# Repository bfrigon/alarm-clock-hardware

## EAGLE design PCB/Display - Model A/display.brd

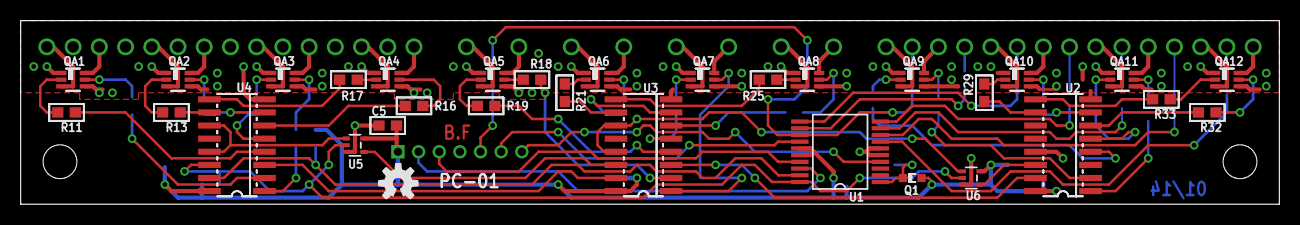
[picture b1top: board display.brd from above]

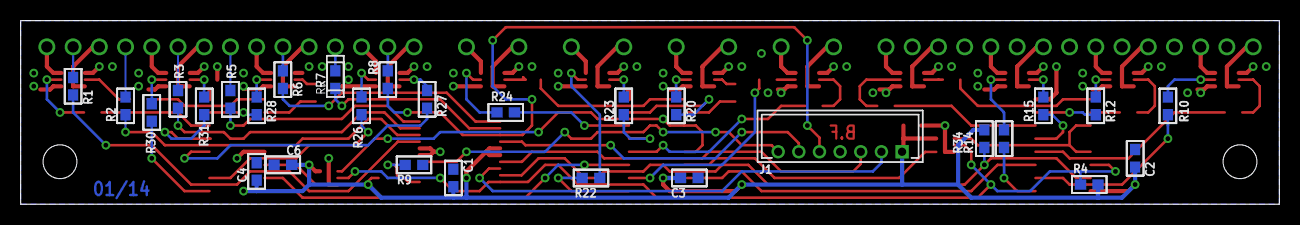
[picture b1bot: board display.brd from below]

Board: 2 copper layers, 121.9 x 17.8 mm, 64 parts (30 on the bottom side), 101 nets.

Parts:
C1, C2, C3, C4, C5, C6: 100nF; SMD_0603
J1: SNG-2MM-HEADER-07-V; DF3X-7P-2DSA
Q1: ALS-PT19
QA1, QA2, QA3, QA4, QA5, QA6, QA7, QA8, QA9, QA10, QA11, QA12: MMDT3904; SOT363
R1, R2, R3, R5, R6, R7, R8: 47; SMD_0603
R4, R10, R11, R12, R13, R14, R15, R16, R17, R18, R19, R20, R21, R22, R23, R24, R25, R26, R27, R28, R29, R30, R31, R32, R33, R34: 1k; SMD_0603
R9: 10k; SMD_0603
U1: PIC16F1826-I/SS; SSOP20
U2, U3, U4: 74HC4017D; SOIC16N
U5, U6: 74LVC1G08DCKR; SC70-5
U$1: LED_MATRIX_V_24X7
U$3: OPENHW_LOGO_150
U$6: INFO_DATE
U$7: INFO_AUTHOR

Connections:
3.3V: C1.1, C2.2, C3.2, C4.2, C5.1, C6.1, J1.1, Q1.C, R4.2, R34.2, U1.15, U1.16, U2.16, U3.16, U4.16, U5.5, U6.5
COL_CLK: R4.1, U1.20, U4.14, U5.2, U6.2
COL_MR: R34.1, U1.19, U4.15
GND: C1.2, C2.1, C3.1, C4.1, C5.2, C6.2, J1.4, QA1.1, QA1.4, QA2.1, QA2.4, QA3.1, QA3.4, QA4.1, QA4.4, QA5.1, QA5.4, QA6.1, QA6.4, QA7.1, QA7.4, QA8.1, QA8.4, QA9.1, QA9.4, QA10.1, QA10.4, QA11.1, QA11.4, QA12.1, QA12.4, R9.1, U1.5, U1.6, U2.8, U2.13, U3.8, U4.8, U5.3, U6.3
unnamed: R8.2, U$1.A7@2
unnamed: R7.2, U$1.A6@2
unnamed: R6.2, U$1.A5@2
unnamed: R5.2, U$1.A4@2
unnamed: R3.2, U$1.A3@2
unnamed: R2.2, U$1.A2@2
unnamed: R1.2, U$1.A1@2
unnamed: Q1.E, R9.2, U1.1
unnamed: QA12.6, U$1.C24
unnamed: QA12.3, U$1.C23
unnamed: QA11.6, U$1.C22
unnamed: QA11.3, U$1.C21
unnamed: QA10.6, U$1.C20
unnamed: QA10.3, U$1.C19
unnamed: QA9.6, U$1.C18
unnamed: QA9.3, U$1.C17
unnamed: QA8.6, U$1.C16
unnamed: QA8.3, U$1.C15
unnamed: QA7.6, U$1.C14
unnamed: QA7.3, U$1.C13
unnamed: QA6.6, U$1.C12
unnamed: QA6.3, U$1.C11
unnamed: QA5.6, U$1.C10
unnamed: QA5.3, U$1.C9
unnamed: QA4.6, U$1.C8
unnamed: QA4.3, U$1.C7
unnamed: QA3.6, U$1.C6
unnamed: QA3.3, U$1.C5
unnamed: QA2.6, U$1.C4
unnamed: QA2.3, U$1.C3
unnamed: QA1.6, U$1.C2
unnamed: QA1.3, U$1.C1
unnamed: QA9.5, R26.2
unnamed: QA9.2, R27.2
unnamed: QA10.5, R28.2
unnamed: QA10.2, R29.2
unnamed: QA11.5, R30.2
unnamed: QA11.2, R31.2
unnamed: QA12.5, R32.2
unnamed: QA12.2, R33.2
unnamed: QA8.2, R25.2
unnamed: QA8.5, R24.2
unnamed: QA7.2, R23.2
unnamed: QA7.5, R22.2
unnamed: QA6.2, R21.2
unnamed: QA6.5, R20.2
unnamed: R10.1, U4.2
unnamed: QA5.2, R19.2
unnamed: QA5.5, R18.2
unnamed: QA4.2, R17.2
unnamed: QA4.5, R16.2
unnamed: QA3.2, R15.2
unnamed: QA3.5, R14.2
unnamed: QA2.2, R13.2
unnamed: QA2.5, R12.2
unnamed: QA1.2, R11.2
unnamed: QA1.5, R10.2
unnamed: U4.11, U4.13, U5.1
unnamed: U3.14, U5.4
unnamed: U3.15, U4.3
unnamed: U2.15, U3.3
unnamed: U3.11, U3.13, U6.1
unnamed: U2.14, U6.4
unnamed: R11.1, U4.4
unnamed: R12.1, U4.7
unnamed: R13.1, U4.10
unnamed: R14.1, U4.1
unnamed: R15.1, U4.5
unnamed: R16.1, U4.6
unnamed: R17.1, U4.9
unnamed: R18.1, U3.2
unnamed: R19.1, U3.4
unnamed: R21.1, U3.10
unnamed: R20.1, U3.7
unnamed: R22.1, U3.1
unnamed: R23.1, U3.5
unnamed: R24.1, U3.6
unnamed: R25.1, U3.9
unnamed: R26.1, U2.2
unnamed: R27.1, U2.4
unnamed: R28.1, U2.7
unnamed: R29.1, U2.10
unnamed: R30.1, U2.1
unnamed: R31.1, U2.5
unnamed: R32.1, U2.6
unnamed: R33.1, U2.9
PGD: J1.6, U1.14
ROW1: R1.1, U1.7
ROW2: R2.1, U1.8
ROW3: R3.1, U1.9
ROW4: R5.1, U1.10
ROW5: R6.1, U1.11
ROW6: R7.1, U1.12
ROW7/PGC: J1.5, R8.1, U1.13
SCL: J1.3, U1.17
SDA: J1.2, U1.18
VPP/!MCLR: J1.7, U1.4

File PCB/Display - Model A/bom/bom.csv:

'Qty.';'Part ID';'Description';'Mfg. SKU';'Manufacturer';'Package';'Value';
'1';'Q1';'Ambiant light sensor';'ALS-PT19-315C/L177/TR8';'Everlight';'ALS-PT19';'-';
'1';'J1';'2mm Single Row Header - 7 pos - SMT Vertical';'DF3X-7P-2DSA';'Hirose Electronic';'DF3X-7P-2DSA';'-';
'2';'U5, U6';'2-input AND gate';'SN74LVC1G08DCKR';'Texas Instruments';'SC70-5';'-';
'3';'U2, U3, U4';'Johnson decade counter';'74HC4017D';'NXP Semiconductors';'SOIC16N';'-';
'12';'QA2, QA1, QA3, QA4, QA5, QA6, QA7, QA8, QA9, QA10, QA11, QA12';'NPN transistor - dual';'MMDT3904-7-F';'Diodes Inc.';'SOT363';'-';
'1';'U1';'20 Pin Flash Microcontroller';'PIC16F1826-I/SS';'Microchip';'SSOP20';'-';
'26';'R4, R10, R11, R12, R13, R14, R15, R16, R17, R18, R19, R20, R21, R22, R23, R24, R25, R26, R27, R28, R29, R30, R31, R32, R33, R34';'Resistor - SMT 0603 - 1k';'-';'-';'SMT 0603';'1k';
'1';'R9';'Resistor - SMT 0603 - 10k';'-';'-';'SMT 0603';'10k';
'7';'R1, R2, R3, R5, R6, R7, R8';'Resistor - SMT 0603 - 47';'-';'-';'SMT 0603';'47';
'6';'C1, C2, C3, C4, C5, C6';'Capacitor - SMT 0603 - 100nF';'-';'-';'SMT 0603';'100nF';

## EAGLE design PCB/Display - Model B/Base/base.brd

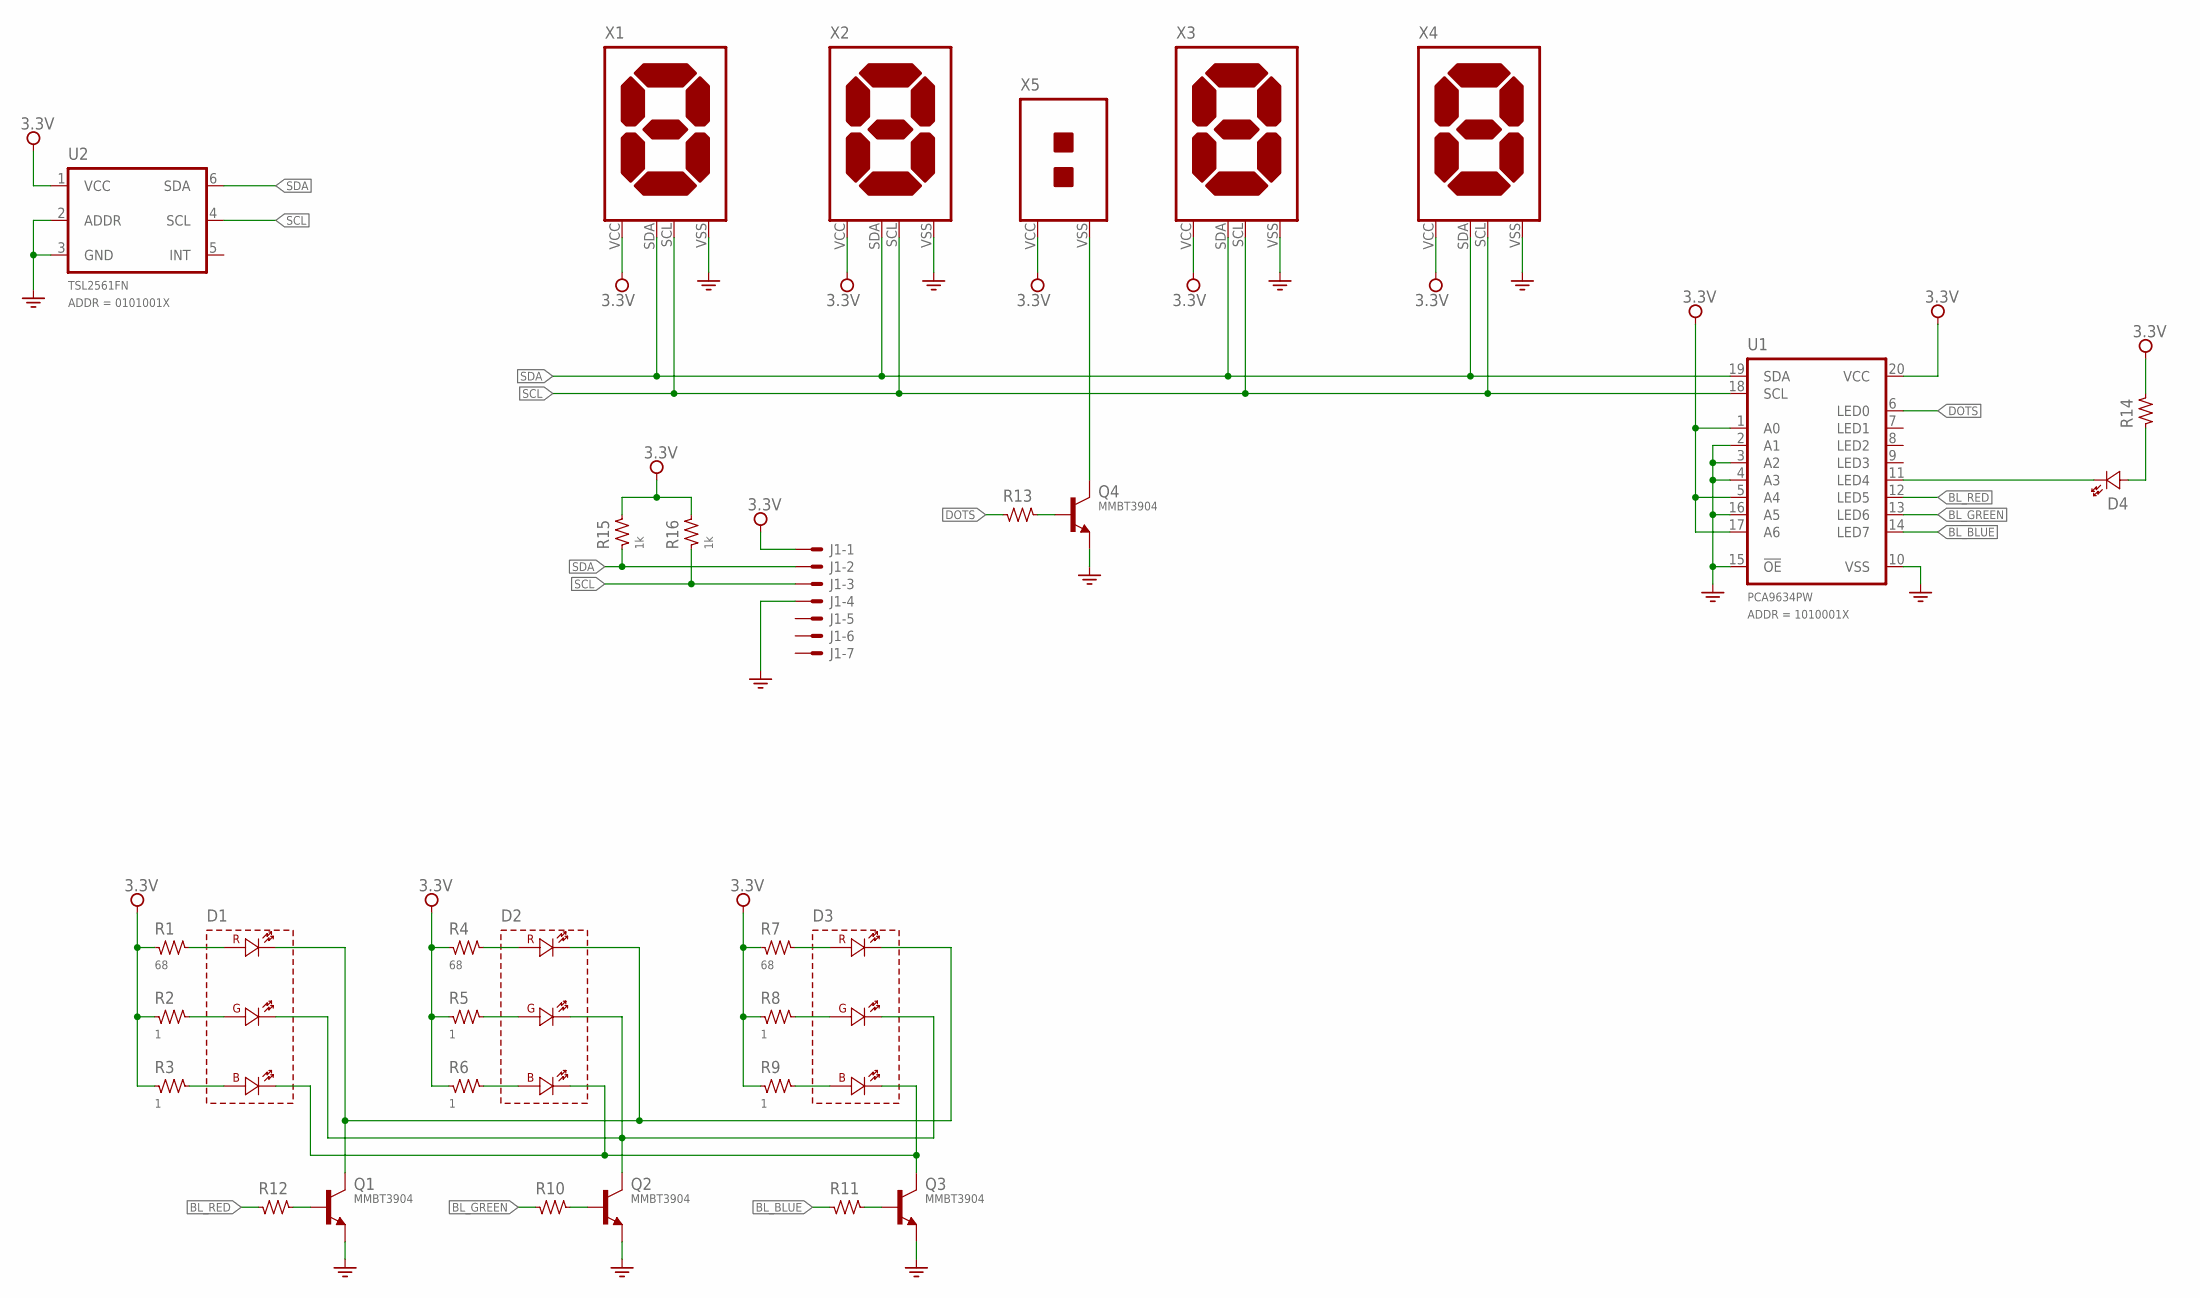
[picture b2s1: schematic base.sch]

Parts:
D1, D2, D3: SMP6-RGB; LED_RGB_PLCC6
D4: {ATTR:COLOR}; LED_3MM
J1: SNG-2MM-HEADER-07-V; DF3X-7P-2DSA; PART_NO DF3A-7P-2DSA
Q1, Q2, Q3, Q4: MMBT3904; SOT23
R1, R4, R7: 68; SMD_0603
R2, R3, R5, R6, R8, R9: 1; SMD_0603
R10, R11, R12, R13, R14: RES-0603; SMD_0603
R15, R16: 1k; SMD_0603
U1: PCA9634PW; TSSOP20
U2: TSL2561FN; DFN-6
X1, X2, X3, X4: CLOCK_LED_SEGMENT
X5: CLOCK_LED_DOTS

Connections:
3.3V: J1.1, R1.1, R2.1, R3.1, R4.1, R5.1, R6.1, R7.1, R8.1, R9.1, R14.2, R15.2, R16.2, U1.1 (A0), U1.5 (A4), U1.17 (A6), U1.20 (VCC), U2.1 (VCC), X1.VCC, X2.VCC, X3.VCC, X4.VCC, X5.VCC
BL_BLUE: R11.1, U1.14 (LED7)
BL_GREEN: R10.1, U1.13 (LED6)
BL_RED: R12.1, U1.12 (LED5)
DOTS: R13.1, U1.6 (LED0)
GND: J1.4, Q1.2 (E), Q2.2 (E), Q3.2 (E), Q4.2 (E), U1.2 (A1), U1.3 (A2), U1.4 (A3), U1.10 (VSS), U1.15 (!OE), U1.16 (A5), U2.2 (ADDR), U2.3 (GND), X1.VSS, X2.VSS, X3.VSS, X4.VSS
unnamed: D1.2 (GA), R2.2
unnamed: D1.4 (RA), R1.2
unnamed: D1.6 (BA), R3.2
unnamed: D2.4 (RA), R4.2
unnamed: D1.1 (GK), D2.1 (GK), D3.1 (GK), Q2.3 (C)
unnamed: D1.5 (BK), D2.5 (BK), D3.5 (BK), Q3.3 (C)
unnamed: D2.2 (GA), R5.2
unnamed: D2.6 (BA), R6.2
unnamed: D3.6 (BA), R9.2
unnamed: D3.2 (GA), R8.2
unnamed: D3.4 (RA), R7.2
unnamed: D1.3 (RK), D2.3 (RK), D3.3 (RK), Q1.3 (C)
unnamed: Q2.1 (B), R10.2
unnamed: Q3.1 (B), R11.2
unnamed: Q4.3 (C), X5.VSS
unnamed: Q4.1 (B), R13.2
unnamed: Q1.1 (B), R12.2
unnamed: D4.K, U1.11 (LED4)
unnamed: D4.A, R14.1
SCL: J1.3, R16.1, U1.18 (SCL), U2.4 (SCL), X1.SCL, X2.SCL, X3.SCL, X4.SCL
SDA: J1.2, R15.1, U1.19 (SDA), U2.6 (SDA), X1.SDA, X2.SDA, X3.SDA, X4.SDA

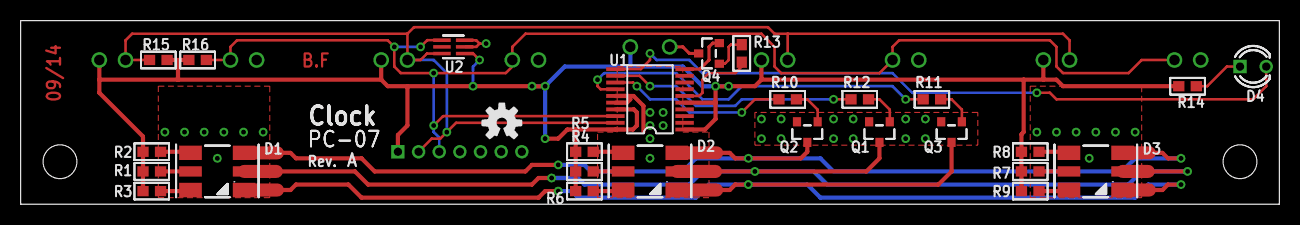
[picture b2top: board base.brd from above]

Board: 2 copper layers, 121.9 x 17.8 mm, 36 parts (1 on the bottom side), 27 nets.

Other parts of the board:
U$1: INFO_DATE
U$3: OPENHW_LOGO_150
U$4: INFO_COMPACT
U$5: INFO_AUTHOR

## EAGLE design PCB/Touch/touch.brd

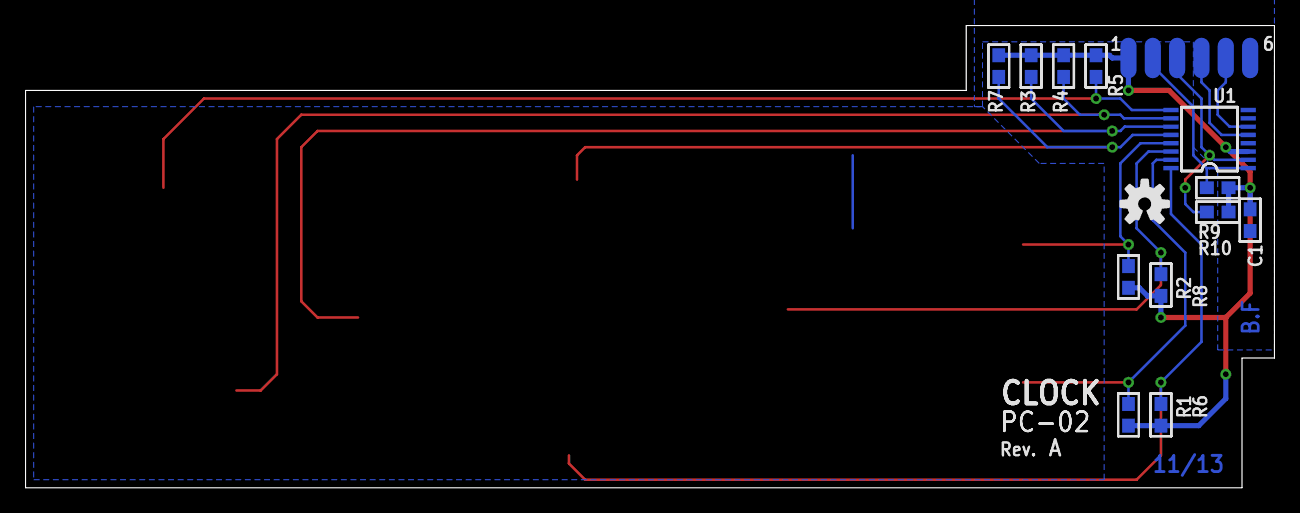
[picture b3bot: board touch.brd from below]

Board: 2 copper layers, 97.8 x 36.2 mm, 22 parts (22 on the bottom side), 14 nets.

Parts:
3.3V: 1; WIRE_SMT
!ATTN: 2; WIRE_SMT
!IRQ: 3; WIRE_SMT
C1: 1uF; SMD_0603
R1, R2, R3, R4, R5, R6, R7, R8: 780k; SMD_0603
R9, R10: 4.7k; SMD_0603
SCL: 4; WIRE_SMT
SDA: 5; WIRE_SMT
U1: MPR084EJ; TSSOP16
U$1: INFO_AUTHOR
U$2: INFO_DATE
U$3: INFO_COMPACT
U$5: OPENHW_LOGO_150
W6: 6; WIRE_SMT

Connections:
3.3V: 3.3V.1, C1.2, R1.2, R2.2, R3.2, R4.2, R5.2, R6.2, R7.2, R8.2, R9.2, R10.2, U1.3
!ATTN: !ATTN.1, R9.1, U1.1
!IRQ: !IRQ.1, R10.1, U1.2
E_ALARM: R4.1, U1.10
E_DOWN: R6.1, U1.16
E_HOUR: R2.1, U1.13
E_LEFT: R8.1, U1.14
E_MIN: R1.1, U1.15
E_RIGHT: R3.1, U1.11
E_TIME: R5.1, U1.9
E_UP: R7.1, U1.12
GND: C1.1, U1.4, U1.7, W6.1
SCL: SCL.1, U1.5
SDA: SDA.1, U1.6

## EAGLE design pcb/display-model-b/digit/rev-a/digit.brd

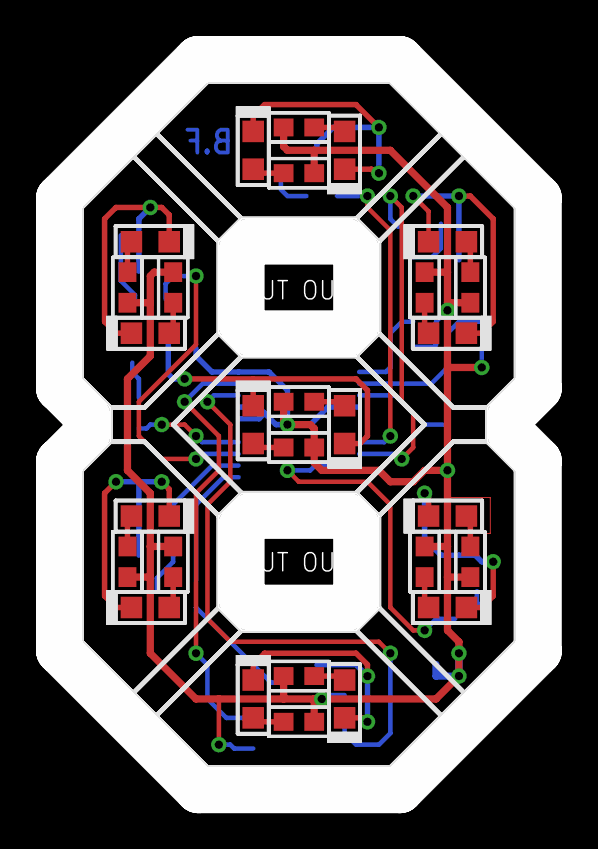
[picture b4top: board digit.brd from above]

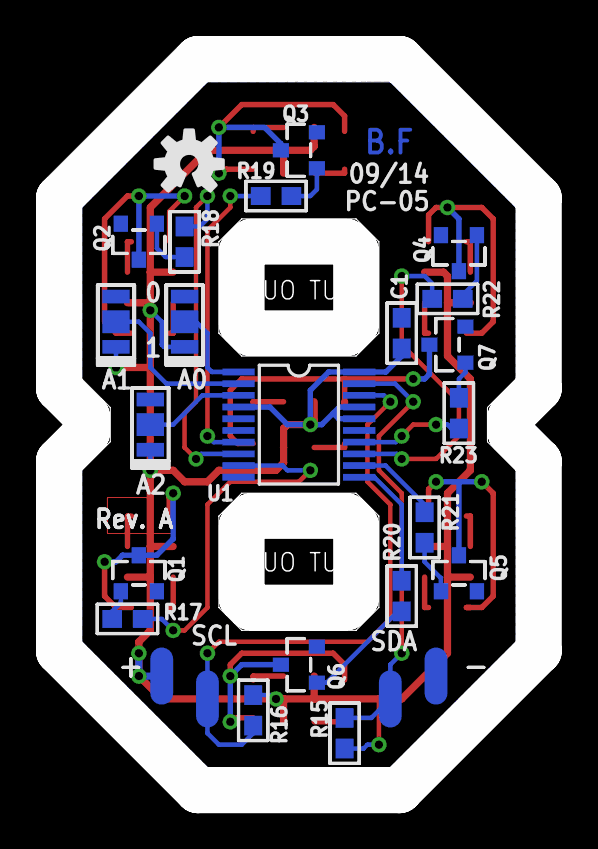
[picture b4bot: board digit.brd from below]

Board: 2 copper layers, 26.7 x 40.6 mm, 55 parts (27 on the bottom side), 42 nets.

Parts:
C1: 100nF; SMD_0603
D1, D2, D3, D4, D5, D6, D7, D8, D9, D10, D11, D12, D13, D14: Red; CHIPLED_0805
J1, J2, J3: SOLDER_JUMPER_3
Q1, Q2, Q3, Q4, Q5, Q6, Q7: MMBT3904; SOT23
R1, R2, R3, R4, R5, R6, R7, R8, R9, R10, R11, R12, R13, R14: 56; SMD_0603
R15, R16: N/A; SMD_0603
R17, R18, R19, R20, R21, R22, R23: 3k; SMD_0603
U1: PCA9634PW; TSSOP20
U$1: OPENHW_LOGO_150
U$2: INFO_AUTHOR
W1, W2, W3, W4: WIRE_SMT

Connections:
3.3V: C1.1, J1.1, J2.1, J3.1, R1.1, R2.1, R3.1, R4.1, R5.1, R6.1, R7.1, R8.1, R9.1, R10.1, R11.1, R12.1, R13.1, R14.1, R15.2, R16.2, U1.4, U1.16, U1.17, U1.20, W1.1
A0: J2.2, U1.1
A1: J1.2, U1.2
A2: J3.2, U1.3
GND: C1.2, J1.3, J2.3, J3.3, Q1.2, Q2.2, Q3.2, Q4.2, Q5.2, Q6.2, Q7.2, U1.5, U1.10, U1.15, W4.1
unnamed: Q1.1, R17.2
unnamed: D7.K, D8.K, Q4.3
unnamed: D13.K, D14.K, Q7.3
unnamed: D1.K, D2.K, Q1.3
unnamed: D3.K, D4.K, Q2.3
unnamed: D5.K, D6.K, Q3.3
unnamed: D3.A, R3.2
unnamed: D4.A, R4.2
unnamed: D14.A, R14.2
unnamed: D13.A, R13.2
unnamed: D2.A, R2.2
unnamed: D1.A, R1.2
unnamed: D5.A, R5.2
unnamed: D6.A, R6.2
unnamed: D11.A, R11.2
unnamed: D9.K, D10.K, Q5.3
unnamed: D11.K, D12.K, Q6.3
unnamed: D12.A, R12.2
unnamed: D10.A, R10.2
unnamed: D9.A, R9.2
unnamed: D7.A, R7.2
unnamed: D8.A, R8.2
unnamed: Q2.1, R18.2
unnamed: Q3.1, R19.2
unnamed: Q6.1, R20.2
unnamed: Q5.1, R21.2
unnamed: Q4.1, R22.2
unnamed: Q7.1, R23.2
SCL: R16.1, U1.18, W3.1
SDA: R15.1, U1.19, W2.1
SEG_A: R19.1, U1.7
SEG_B: R18.1, U1.8
SEG_C: R17.1, U1.9
SEG_D: R20.1, U1.11
SEG_E: R21.1, U1.12
SEG_F: R22.1, U1.13
SEG_G: R23.1, U1.14

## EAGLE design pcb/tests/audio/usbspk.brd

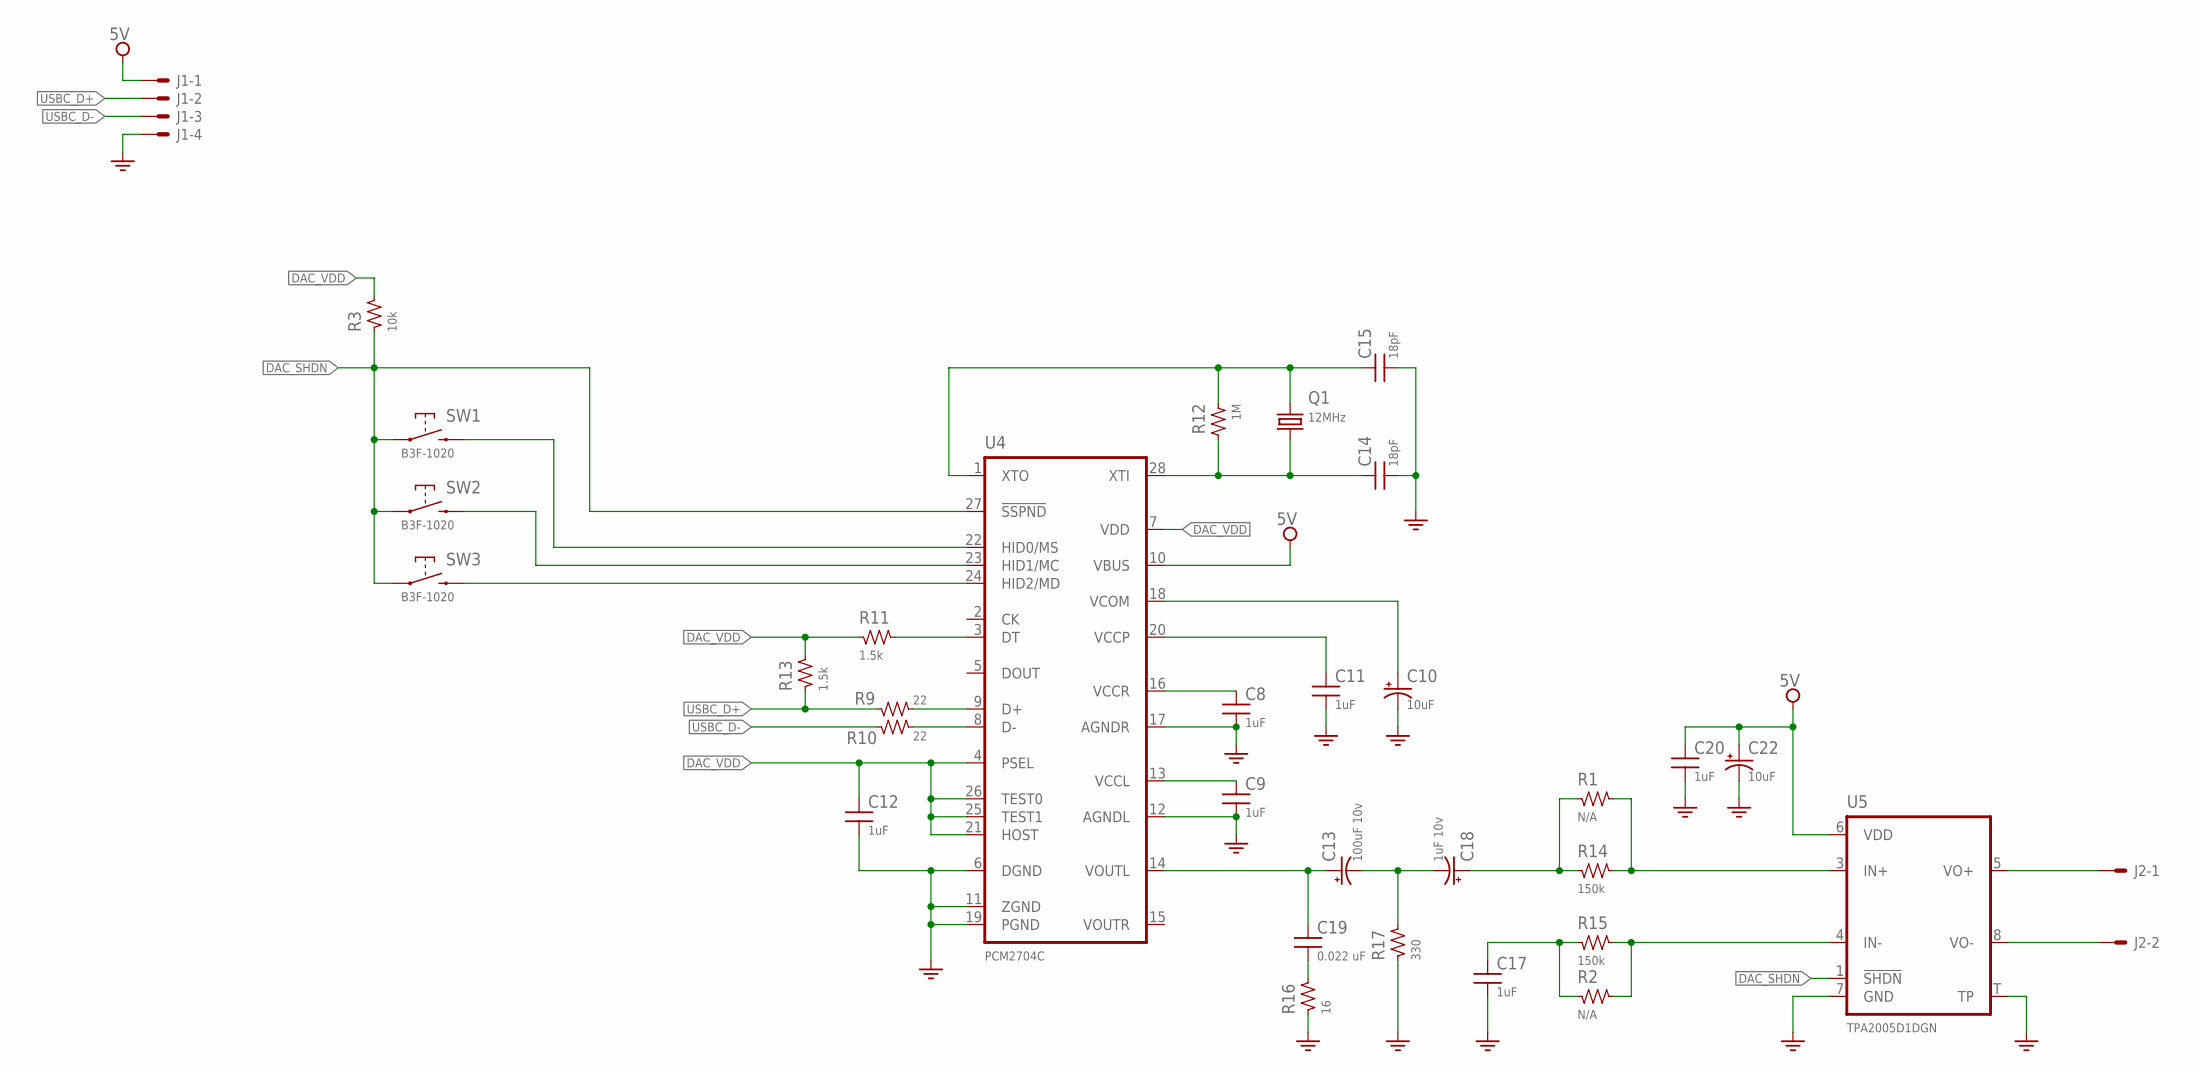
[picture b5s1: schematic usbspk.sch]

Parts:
C8, C9, C11, C12, C17, C20: 1uF; SMD_0603
C10, C22: 10uF; CAP_S0805
C13: 100uF 10v; CAP_S1210
C14, C15: 18pF; SMD_0603
C18: 1uF 10v; CAP_S0805
C19: 0.022 uF; SMD_0603
J1: SNG-100-HEADER-04-HDR-V; HDR_M_4
J2: SNG-100-HEADER-02-FL-V; 22-23-2021
Q1: 12MHz; HC49/S; PART_NO 9C-12.000MEEJ-T
R1, R2: N/A; SMD_0603
R3: 10k; SMD_0603
R9, R10: 22; SMD_0603
R11, R13: 1.5k; SMD_0603
R12: 1M; SMD_0603
R14, R15: 150k; SMD_0603
R16: 16; SMD_0603
R17: 330; SMD_0603
SW1, SW2, SW3: B3F-1020; B3F-10XX
U4: PCM2704C; TSSOP28
U5: TPA2005D1DGN; PPSOP8

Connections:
5V: C20.1, C22.+, J1.1, U4.10 (VBUS), U5.6 (VDD)
DAC_SHDN: R3.1, SW1.3 (1), SW1.4 (1), SW2.3 (1), SW2.4 (1), SW3.3 (1), SW3.4 (1), U4.27 (!SSPND), U5.1 (!SHDN)
DAC_VDD: C12.1, R3.2, R11.1, R13.2, U4.4 (PSEL), U4.7 (VDD), U4.21 (HOST), U4.25 (TEST1), U4.26 (TEST0)
GND: C8.2, C9.2, C10.-, C11.2, C12.2, C14.2, C15.2, C17.2, C20.2, C22.-, J1.4, R16.1, R17.1, U4.6 (DGND), U4.11 (ZGND), U4.12 (AGNDL), U4.17 (AGNDR), U4.19 (PGND), U5.7 (GND), U5.T (TP)
unnamed: R9.2, U4.9 (D+)
unnamed: R10.2, U4.8 (D-)
unnamed: C9.1, U4.13 (VCCL)
unnamed: C10.+, U4.18 (VCOM)
unnamed: C11.1, U4.20 (VCCP)
unnamed: C8.1, U4.16 (VCCR)
unnamed: C18.+, R1.1, R14.1
unnamed: R11.2, U4.3 (DT)
unnamed: SW1.1 (2), SW1.2, U4.22 (HID0/MS)
unnamed: SW2.1 (2), SW2.2, U4.23 (HID1/MC)
unnamed: SW3.1 (2), SW3.2, U4.24 (HID2/MD)
unnamed: C13.+, C19.1, U4.14 (VOUTL)
unnamed: J2.1, U5.5 (VO+)
unnamed: J2.2, U5.8 (VO-)
unnamed: R1.2, R14.2, U5.3 (IN+)
unnamed: R2.2, R15.2, U5.4 (IN-)
unnamed: C17.1, R2.1, R15.1
unnamed: C13.-, C18.-, R17.2
unnamed: C19.2, R16.2
USBC_D+: J1.2, R9.1, R13.1
USBC_D-: J1.3, R10.1
XTI: C14.1, Q1.2, R12.2, U4.28 (XTI)
XTO: C15.1, Q1.1, R12.1, U4.1 (XTO)

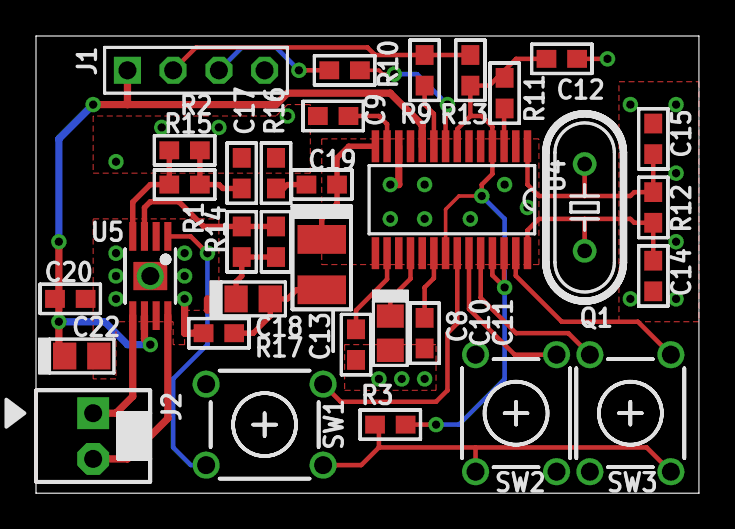
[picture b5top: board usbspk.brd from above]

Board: 2 copper layers, 36.8 x 25.4 mm, 34 parts (1 on the bottom side), 27 nets.

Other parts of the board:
U$1: INFO_COMPACT

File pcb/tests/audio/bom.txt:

**********************************************************************************
*                                BILL OF MATERIAL                                *
**********************************************************************************

Last mod. : 2015-01-05 14:14:17
Doc. ID   : CLK-SCH-50
Project   : ALARM CLOCK
Title     : PCM2704 + TPA2005
            EVAL
Part #    : CLK-PC-03-AUD
REV.      : A


Qty | Names              | Description                    | Mfg. SKU        | Package      | Value     
=======================================================================================================
  1 | Q1                 | Crystal                        | 9C-12.000MEEJ-T | HC49/S       | 12MHz     
----|--------------------|--------------------------------|-----------------|--------------|-----------
  3 | SW1-SW3            | Tactile switch - 6x6mm - 5mm   | B3F-1020        | B3F-10XX     | --        
    |                    | Pitch - 100g                   |                 |              |           
----|--------------------|--------------------------------|-----------------|--------------|-----------
  1 | C19                | Capacitor - SMT 0603 - 0.022   | CAP-0603        | SMT 0603     | 0.022 uF  
    |                    | uF                             |                 |              |           
----|--------------------|--------------------------------|-----------------|--------------|-----------
  2 | C14-C15            | Capacitor - SMT 0603 - 18pF    | CAP-0603        | SMT 0603     | 18pF      
----|--------------------|--------------------------------|-----------------|--------------|-----------
  6 | C8-C9, C11-C12,    | Capacitor - SMT 0603 - 1uF     | CAP-0603        | SMT 0603     | 1uF       
    | C17, C20           |                                |                 |              |           
----|--------------------|--------------------------------|-----------------|--------------|-----------
  2 | C10, C22           | Electrolytic capacitor - SMT   | CAP-E-S0805     | CAP_S0805    | 10uF      
    |                    | 0805 - 10uF                    |                 |              |           
----|--------------------|--------------------------------|-----------------|--------------|-----------
  1 | C18                | Electrolytic capacitor - SMT   | CAP-E-S0805     | CAP_S0805    | 1uF 10v   
    |                    | 0805 - 1uF 10v                 |                 |              |           
----|--------------------|--------------------------------|-----------------|--------------|-----------
  1 | C13                | Electrolytic capacitor - SMT   | CAP-E-S1210     | CAP_S1210    | 100uF 10v 
    |                    | 1210 - 100uF 10v               |                 |              |           
----|--------------------|--------------------------------|-----------------|--------------|-----------
  1 | U4                 |                                | PCM2704C        | TSSOP28      | --        
----|--------------------|--------------------------------|-----------------|--------------|-----------
  2 | R11, R13           | Resistor - SMT 0603 - 1.5k     | RES-0603        | SMT 0603     | 1.5k      
----|--------------------|--------------------------------|-----------------|--------------|-----------
  1 | R3                 | Resistor - SMT 0603 - 10k      | RES-0603        | SMT 0603     | 10k       
----|--------------------|--------------------------------|-----------------|--------------|-----------
  2 | R14-R15            | Resistor - SMT 0603 - 150k     | RES-0603        | SMT 0603     | 150k      
----|--------------------|--------------------------------|-----------------|--------------|-----------
  1 | R16                | Resistor - SMT 0603 - 16       | RES-0603        | SMT 0603     | 16        
----|--------------------|--------------------------------|-----------------|--------------|-----------
  1 | R12                | Resistor - SMT 0603 - 1M       | RES-0603        | SMT 0603     | 1M        
----|--------------------|--------------------------------|-----------------|--------------|-----------
  2 | R9-R10             | Resistor - SMT 0603 - 22       | RES-0603        | SMT 0603     | 22        
----|--------------------|--------------------------------|-----------------|--------------|-----------
  1 | R17                | Resistor - SMT 0603 - 330      | RES-0603        | SMT 0603     | 330       
----|--------------------|--------------------------------|-----------------|--------------|-----------
  1 | J2                 | 2 Pos - Single Row - 2.54mm    | SNG-100-HEADER- | 22-23-2021   | --        
    |                    | header - Vertical              | 02-FL-V         |              |           
----|--------------------|--------------------------------|-----------------|--------------|-----------
  1 | J1                 | 4 Pos - Single Row - 2.54mm    | SNG-100-HEADER- | HDR_M_4      | --        
    |                    | header                         | 04-HDR-V        |              |           
----|--------------------|--------------------------------|-----------------|--------------|-----------
  1 | U5                 |                                | TPA2005D1DGN    | PPSOP8       | --        
----|--------------------|--------------------------------|-----------------|--------------|-----------

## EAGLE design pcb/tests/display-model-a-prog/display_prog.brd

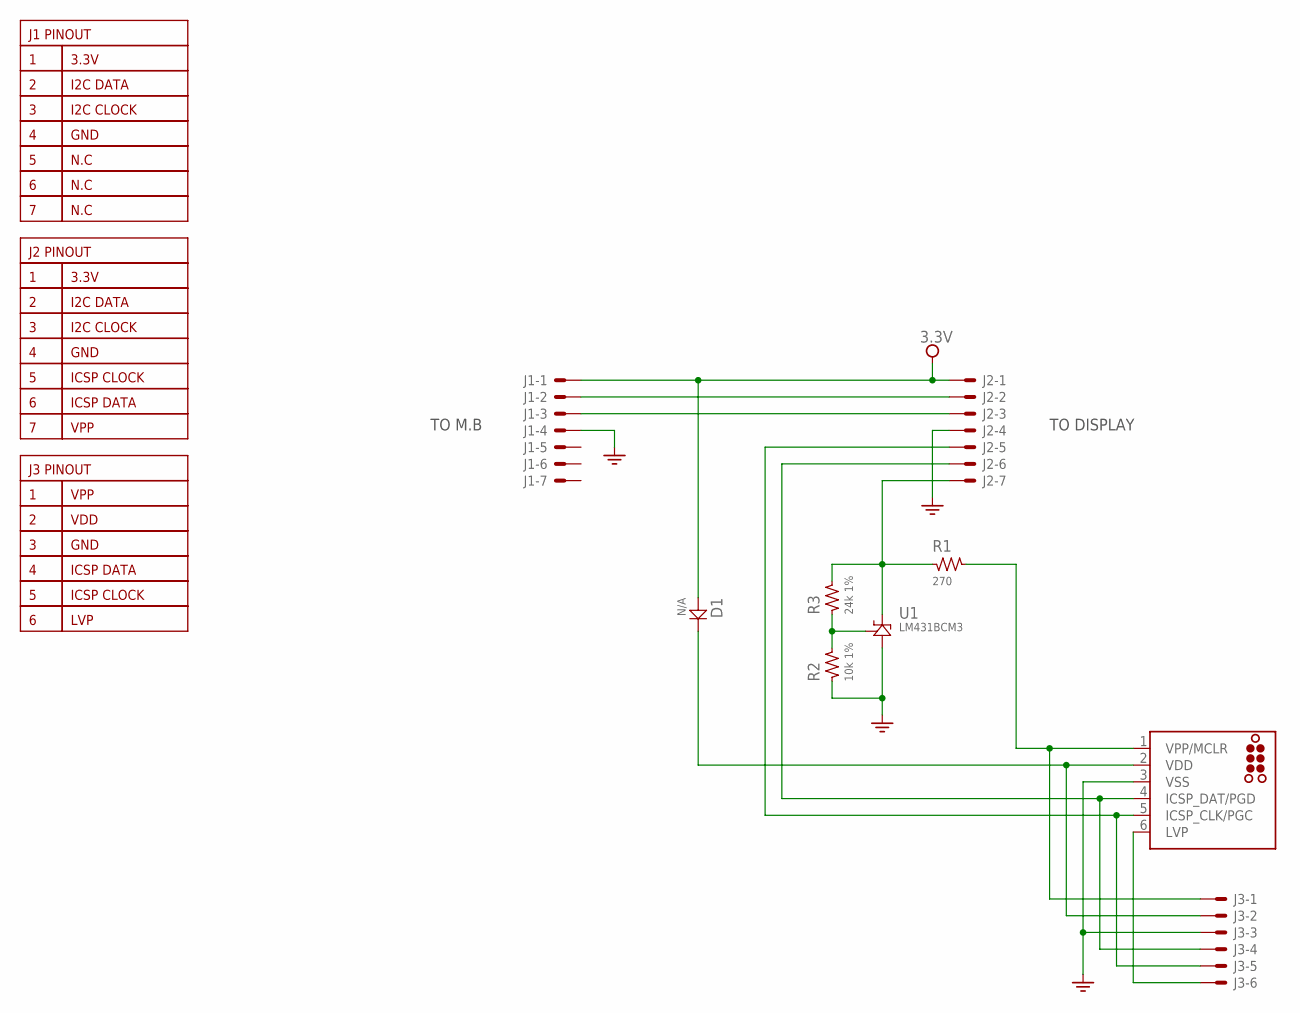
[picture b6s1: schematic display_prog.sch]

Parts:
D1: N/A; DIODE_0603
J1, J2: SNG-2MM-HEADER-07-V; DF3X-7P-2DSA
J3: SNG-100-HEADER-06-FL-V; 22-23-2061
J4: TC2030-MCP
R1: 270; SMD_0603
R2: 10k 1%; SMD_0603
R3: 24k 1%; SMD_0603
U1: LM431BCM3; SOT23

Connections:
3.3V: D1.A, J1.1, J2.1
GND: J1.4, J2.4, J3.3, J4.3 (VSS), R2.1, U1.3 (A)
ICSP-CLK: J2.5, J3.5, J4.5 (ICSP_CLK/PGC)
ICSP-DAT: J2.6, J3.4, J4.4 (ICSP_DAT/PGD)
unnamed: J3.1, J4.1 (VPP/MCLR), R1.2
unnamed: R2.2, R3.1, U1.2 (ADJ)
unnamed: J2.7, R1.1, R3.2, U1.1 (K)
unnamed: J3.6, J4.6 (LVP)
SCL: J1.3, J2.3
SDA: J1.2, J2.2
VDD_MON: D1.K, J3.2, J4.2 (VDD)

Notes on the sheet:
TO DISPLAY
TO M.B

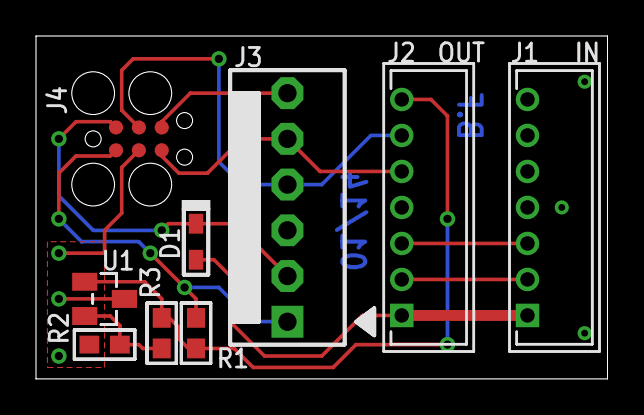
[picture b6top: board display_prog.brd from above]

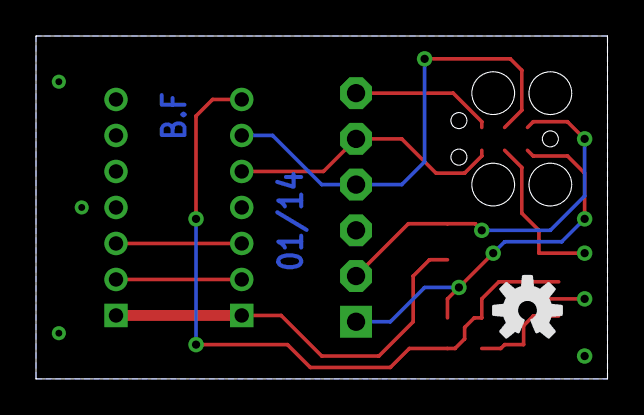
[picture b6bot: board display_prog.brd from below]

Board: 2 copper layers, 31.8 x 19.1 mm, 12 parts (3 on the bottom side), 11 nets.

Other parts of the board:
U$1: OPENHW_LOGO_150
U$2: INFO_AUTHOR
U$3: INFO_DATE

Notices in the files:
parts and their libraries:
Connectors: ©2009 ROFA.cz
